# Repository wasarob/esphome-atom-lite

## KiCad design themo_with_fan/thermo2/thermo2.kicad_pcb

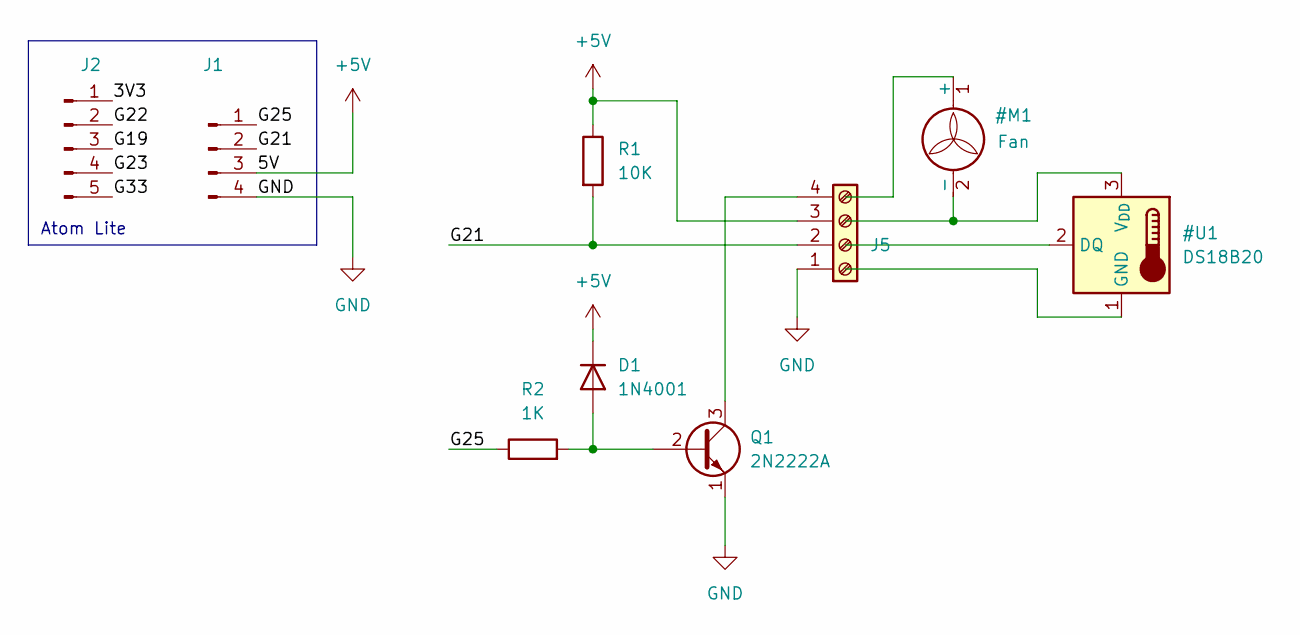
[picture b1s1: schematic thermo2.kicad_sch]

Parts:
D1: 1N4001; D_DO-41_SOD81_P3.81mm_Vertical_AnodeUp
J1: Conn_01x04_Pin; PinHeader_1x04_P2.54mm_Vertical
J2: Conn_01x05_Pin; PinHeader_1x05_P2.54mm_Vertical
J5: Screw_Terminal_01x04; JST_VH_B4P-VH_1x04_P3.96mm_Vertical
Q1: 2N2222A; TO-92_Inline
R1: 10K; R_Axial_DIN0207_L6.3mm_D2.5mm_P2.54mm_Vertical
R2: 1K; R_Axial_DIN0207_L6.3mm_D2.5mm_P2.54mm_Vertical

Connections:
+5V: D1.1 (K), J1.3, J5.3, R1.1
/3V3: J2.1
/G19: J2.3
/G21: J1.2, J5.2, R1.2
/G22: J2.2
/G23: J2.4
/G25: J1.1, R2.1
/G33: J2.5
GND: J1.4, J5.1, Q1.1 (E)
unnamed: D1.2 (A), Q1.2 (B), R2.2
unnamed: J5.4, Q1.3 (C)

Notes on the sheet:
Atom Lite

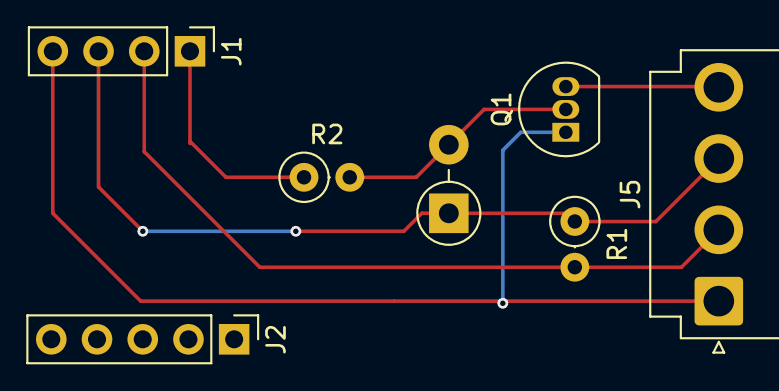
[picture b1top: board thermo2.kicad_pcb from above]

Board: 2 copper layers, 7 parts (0 on the bottom side), 6 nets.

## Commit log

2024-07-28 added dallas fan config + circuit
2024-07-28 added dallas example
2024-07-28 added correct kicad files
